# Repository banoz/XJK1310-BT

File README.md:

# XJK1310-BT
Adding Bluetooth to XJK1310 scales

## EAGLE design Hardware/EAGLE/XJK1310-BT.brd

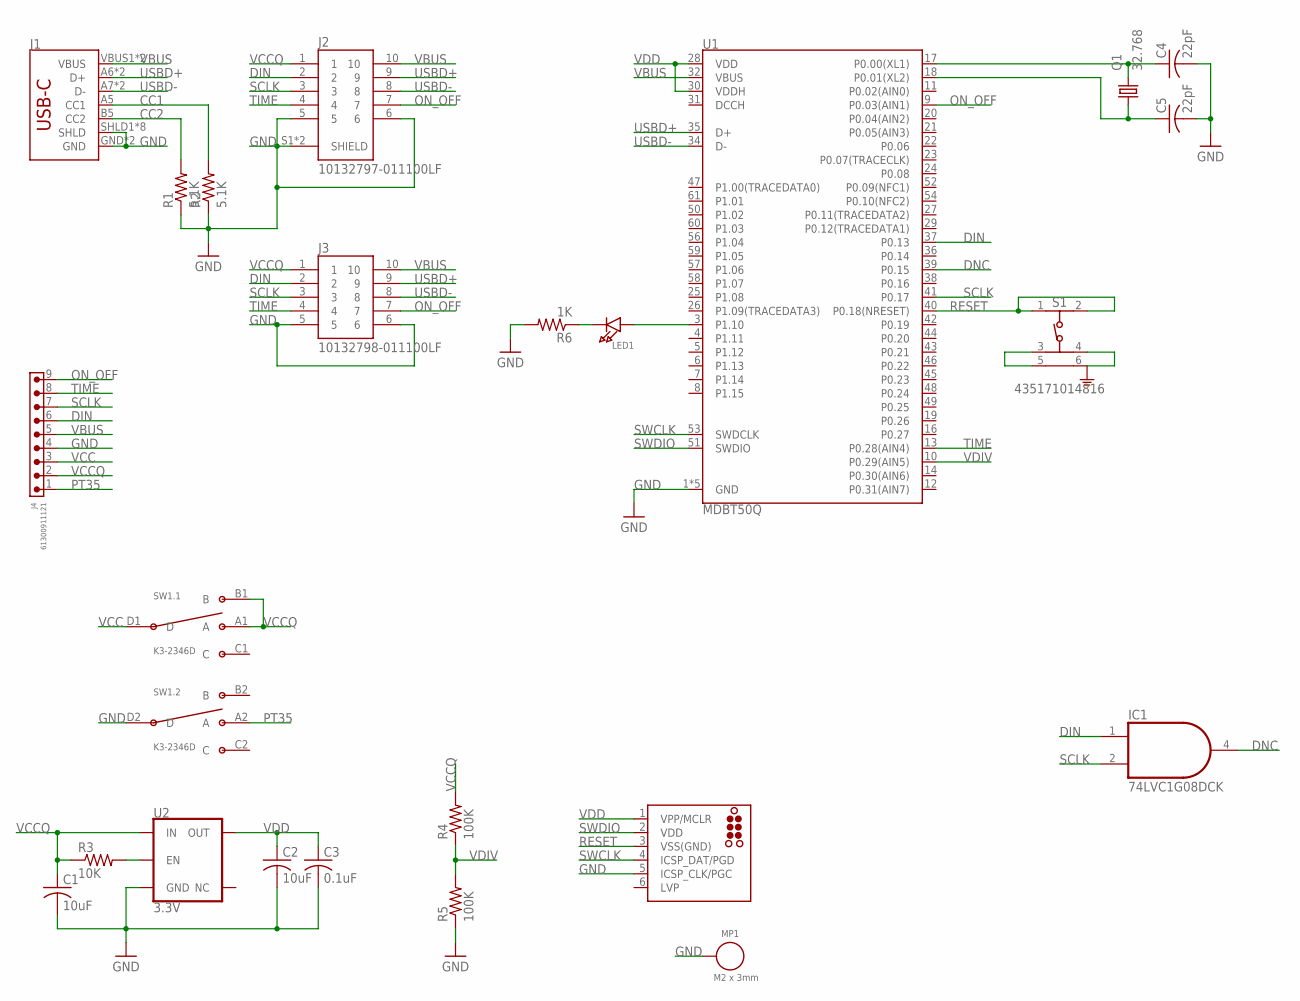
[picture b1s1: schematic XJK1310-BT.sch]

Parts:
C1, C2: 10uF; C0603; LCSC C86275
C3: 0.1uF; C0603; LCSC C1591
C4, C5: 22pF; C0402; LCSC C106203
IC1: 74LVC1G08DCK; SC70-5; LCSC C7832
J1: USB_C5; USB-C-16P-5; LCSC C393939
J2: 10132797-011100LF; AMPHENOL_10132797-011100LF; LCSC C3654689
J3: 10132798-011100LF; AMPHENOL_10132798-011100LF; LCSC C5338055
J4: 61300911121
J5: TC2030-MCP-NL
LED1: LED0805_NOOUTLINE; CHIPLED_0805_NOOUTLINE; LCSC C2297
MP1: M2 x 3mm; WA-SMSI_9774030243; LCSC C36498713
Q1: 32.768; 3.2X1.5; LCSC C32346
R1, R2: 5.1K; R0402; LCSC C105872
R3: 10K; R0402; LCSC C60490
R4, R5: 100K; R0402; LCSC C60491
R6: 1K; R0402; LCSC C106235
S1: 435171014816; LCSC C390649
SW1: K3-2346D; LCSC C145839
U1: MDBT50Q; LCSC C5118826
U2: 3.3V; SOT23-5; LCSC C51118

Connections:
CC1: J1.A5 (CC1), R2.2
CC2: J1.B5 (CC2), R1.2
DIN: IC1.1 (I0), J2.2, J3.2, J4.6, U1.37 (P0.13)
DNC: IC1.4 (O), U1.39 (P0.15)
GND: C1.2, C2.2, C3.2, C4.2, C5.2, IC1.3 (GND), J1.GND, J1.GND2 (GND), J1.SHLD1 (SHLD), J1.SHLD2 (SHLD), J1.SHLD3 (SHLD), J1.SHLD4 (SHLD), J1.SHLD5 (SHLD), J1.SHLD6 (SHLD), J1.SHLD7 (SHLD), J1.SHLD8 (SHLD), J2.5, J2.6, J2.S1 (SHIELD), J2.S2 (SHIELD), J3.5, J3.6, J4.4, J5.5 (ICSP_CLK/PGC), MP1.1, R1.1, R2.1, R5.1, R6.2, S1.3, S1.4, S1.5, S1.6, SW1.D2 (D), U1.1 (GND), U1.2 (GND), U1.15 (GND), U1.33 (GND), U1.55 (GND), U2.2 (GND)
unnamed: C4.1, Q1.2, U1.17 (P0.00(XL1))
unnamed: C5.1, Q1.1, U1.18 (P0.01(XL2))
unnamed: R3.2, U2.3 (EN)
unnamed: LED1.A, U1.3 (P1.10)
unnamed: LED1.C, R6.1
ON_OFF: J2.7, J3.7, J4.9, U1.9 (P0.03(AIN1))
PT35: J4.1, SW1.A2 (A)
RESET: J5.3 (VSS(GND)), S1.1, S1.2, U1.40 (P0.18(NRESET))
SCLK: IC1.2 (I1), J2.3, J3.3, J4.7, U1.41 (P0.17)
SWCLK: J5.4 (ICSP_DAT/PGD), U1.53 (SWDCLK)
SWDIO: J5.2 (VDD), U1.51 (SWDIO)
TIME: J2.4, J3.4, J4.8, U1.13 (P0.28(AIN4))
USBD+: J1.A6 (D+), J1.B6 (D+), J2.9, J3.9, U1.35 (D+)
USBD-: J1.A7 (D-), J1.B7 (D-), J2.8, J3.8, U1.34 (D-)
VBUS: J1.VBUS1 (VBUS), J1.VBUS2 (VBUS), J2.10, J3.10, J4.5, U1.32 (VBUS)
VCC: IC1.5 (VCC), J4.3, SW1.D1 (D)
VCCQ: C1.1, J2.1, J3.1, J4.2, R3.1, R4.2, SW1.A1 (A), SW1.B1 (B), U2.1 (IN)
VDD: C2.1, C3.1, J5.1 (VPP/MCLR), U1.28 (VDD), U1.30 (VDDH), U2.5 (OUT)
VDIV: R4.1, R5.2, U1.10 (P0.29(AIN5))

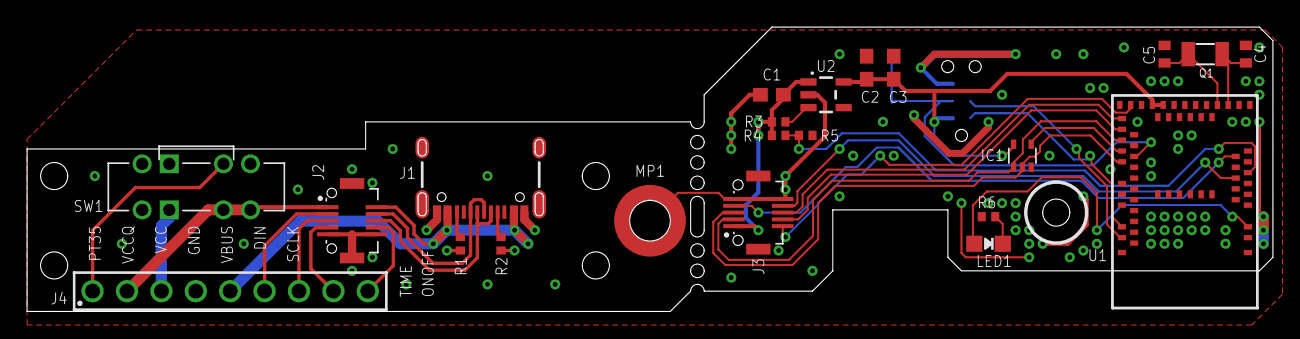
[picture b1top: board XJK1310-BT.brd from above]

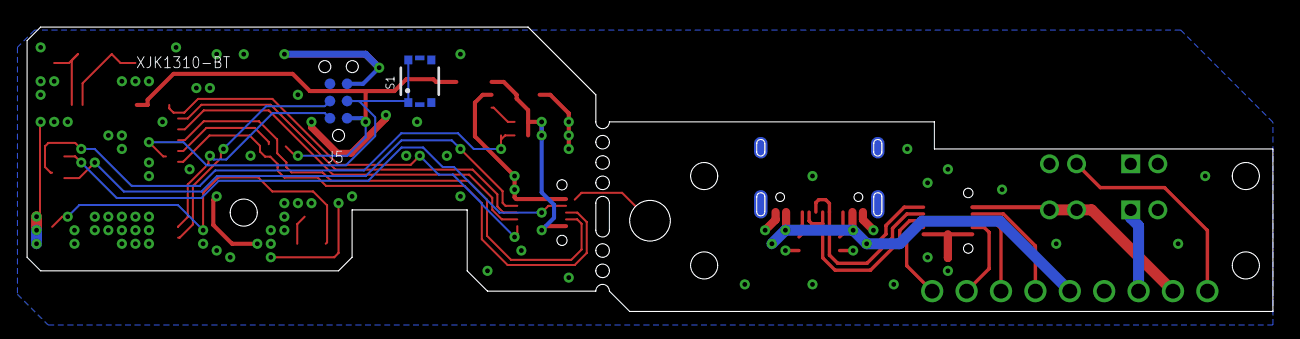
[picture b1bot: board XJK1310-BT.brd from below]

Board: 2 copper layers, 92.0 x 21.0 mm, 24 parts (2 on the bottom side), 24 nets.

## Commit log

2025-04-04 Sleep mode fix
2025-04-06 Silkscreen change
2025-04-29 DAT restore
2025-05-02 rearrange

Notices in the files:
parts and their libraries:
Wurth_Assembly_WA-SMSI: Copyright: Würth Elektronik
tag-connect: ©2009 ROFA.cz - modified and updated by Robert Darlington ‹rdarlington@gmail.com›
SparkFun-IC-Power: Licensing: Creative Commons ShareAlike 4.0 International - https://creativecommons.org/licenses/by-sa/4.0
